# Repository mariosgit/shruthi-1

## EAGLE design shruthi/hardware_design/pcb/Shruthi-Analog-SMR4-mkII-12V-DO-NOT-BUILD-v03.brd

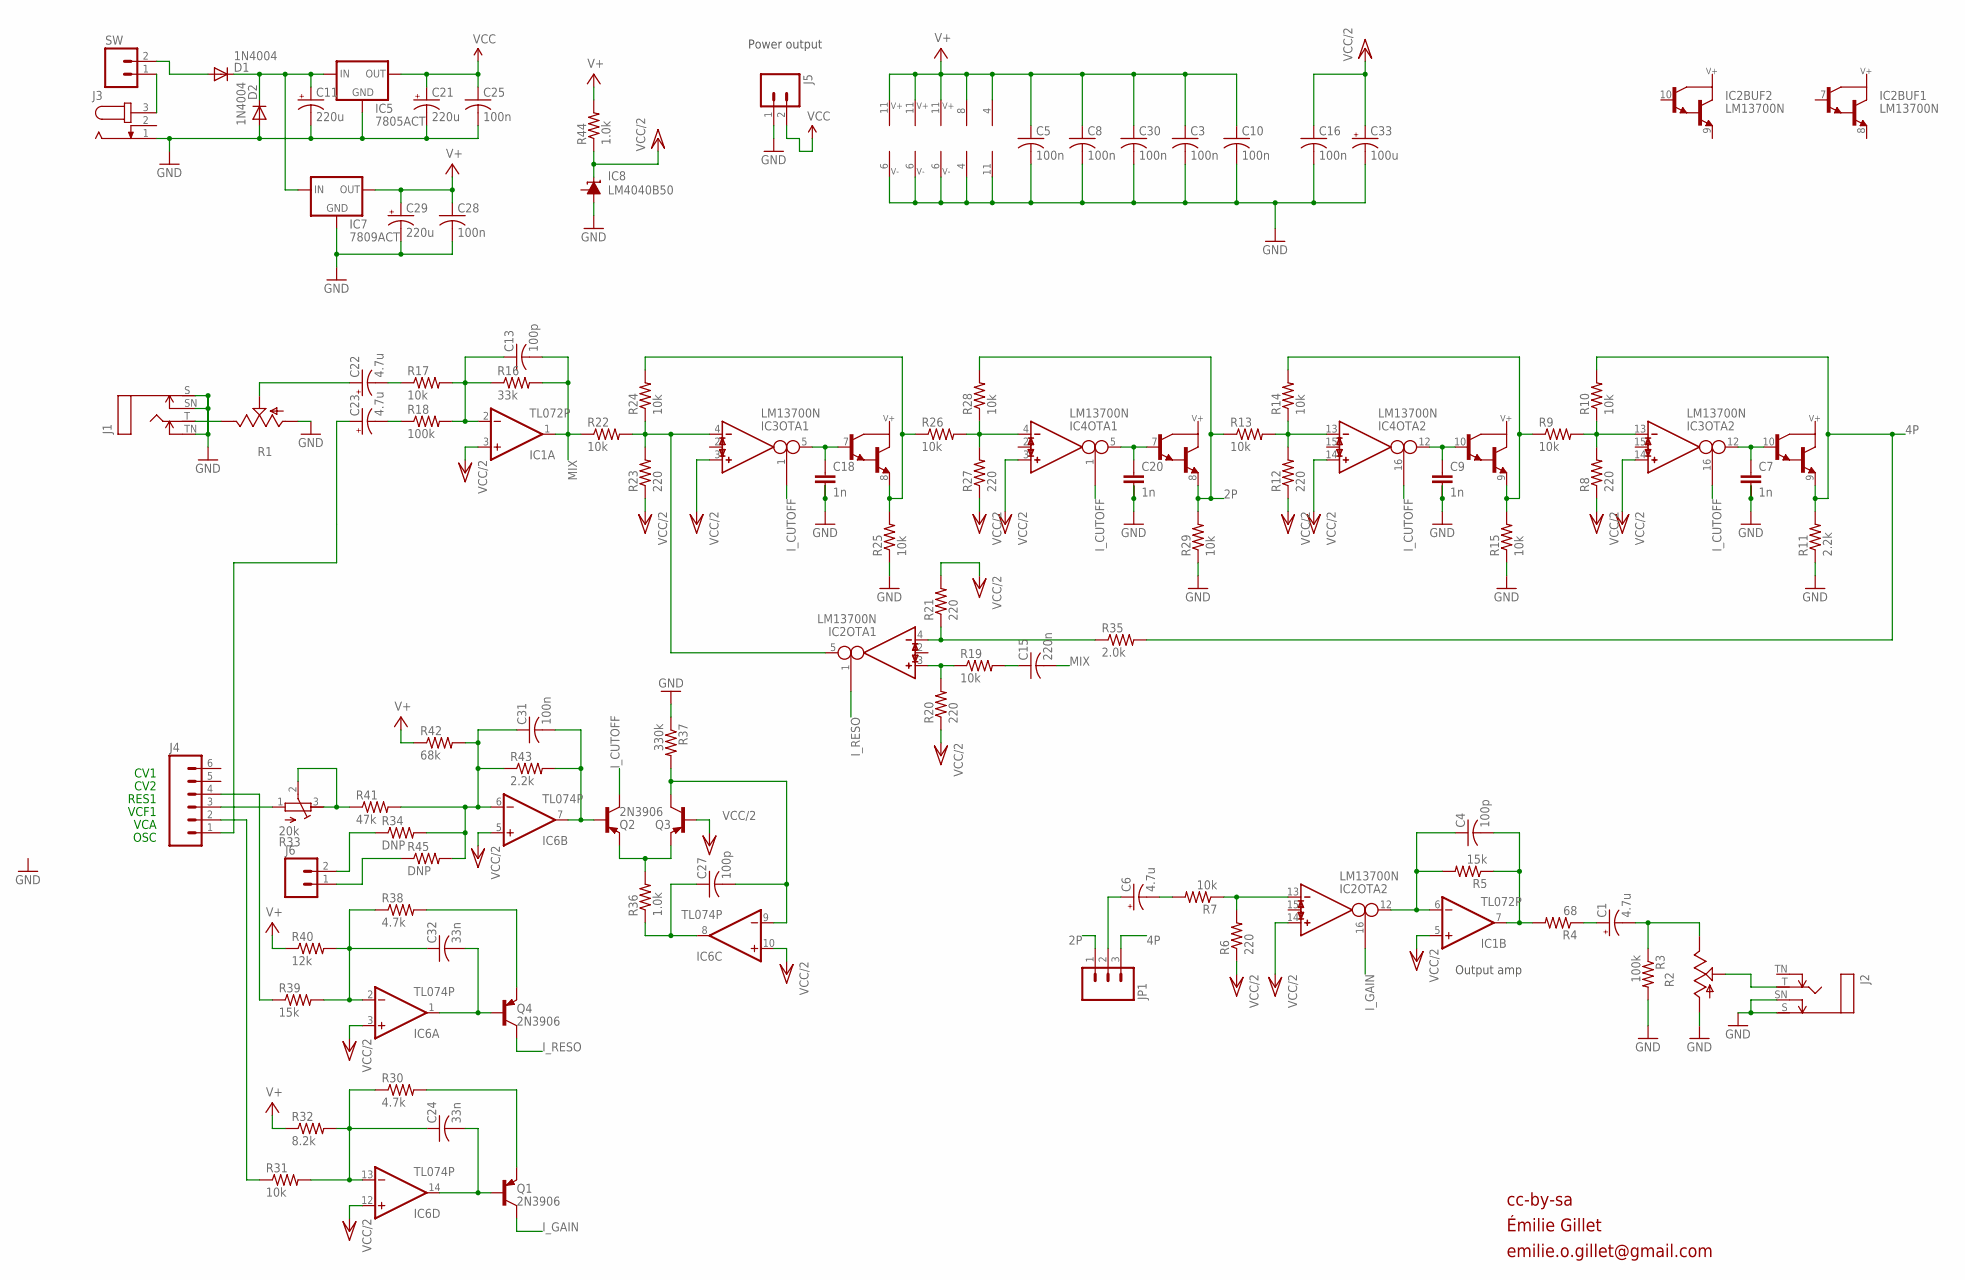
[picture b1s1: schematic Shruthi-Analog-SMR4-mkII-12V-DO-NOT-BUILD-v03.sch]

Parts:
C1, C6, C22, C23: 4.7u; E2,5-6
C3, C5, C8, C10, C16, C25, C28, C30, C31: 100n; C025-025X050
C4, C13, C27: 100p; C025-025X050
C7, C9, C18, C20: 1n; C2.5/5-2
C11, C21, C29: 220u; E5-10,5
C15: 220n; C025-025X050
C24, C32: 33n; C050-025X075
C33: 100u; E2,5-6
D1, D2: 1N4004; DO41-10
IC1: TL072P; DIL08
IC2, IC3, IC4: LM13700N; DIL16
IC5: 7805ACT; 78XXS
IC6: TL074P; DIL14
IC7: 7809ACT; 78XXS
IC8: LM4040B50; LP_O-PBCY-W3
J1, J2: MONOSWS; NMJ4HC-S
J3: JACK-PLUG2; SPC4078_BIG_HOLES
J4: M06SIP; 1X06
J5, J6: M02PTH; 1X02
JP1: M03PTH; 1X03
Q1, Q2, Q3, Q4: 2N3906; TO92-
R1, R2: POT_USCABLED; CABLE_POT_6MM
R3, R18: 100k; 0204/7
R4: 68; 0204/7
R5, R39: 15k; 0204/7
R6, R8, R12, R20, R21, R23, R27: 220; 0204/7
R7, R9, R10, R13, R14, R15, R17, R19, R22, R24, R25, R26, R28, R29, R31: 10k; 0204/7
R11, R43: 2.2k; 0204/7
R16: 33k; 0204/7
R30, R38: 4.7k; 0204/7
R32: 8.2k; 0204/7
R33: 20k; RTRIM3296W
R34, R45: DNP; 0204V
R35: 2.0k; 0204/7
R36, R44: 1.0k; 0204/7
R37: 330k; 0204/7
R40: 12k; 0204/7
R41: 47k; 0204/7
R42: 68k; 0204/7
SW: M02PTH; 1X02

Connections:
2P: IC4.8 (E), JP1.1, R13.1, R28.2, R29.2
4P: IC3.9 (E), JP1.3, R10.2, R11.2, R35.2
GND: C3.2, C5.2, C7.2, C7.3, C8.2, C9.2, C9.3, C10.2, C11.-, C16.2, C18.2, C18.3, C20.2, C20.3, C21.-, C25.2, C28.2, C29.-, C30.2, C33.-, D2.A, IC1.4 (V-), IC2.6 (V-), IC3.6 (V-), IC4.6 (V-), IC5.GND, IC6.11 (V-), IC7.GND, IC8.3 (A), J1.S, J1.SN, J1.TN, J2.S, J2.SN, J3.1, J5.1, R1.A, R2.A, R3.2, R11.1, R15.1, R25.1, R29.1, R37.1
I_CUTOFF: IC3.1 (I_BIAS), IC3.16 (I_BIAS), IC4.1 (I_BIAS), IC4.16 (I_BIAS), Q2.1 (C)
I_GAIN: IC2.16 (I_BIAS), Q1.1 (C)
I_RESO: IC2.1 (I_BIAS), Q4.1 (C)
MIX: C13.2, C15.2, IC1.1 (OUT), R16.2, R22.1
unnamed: D1.A, SW.2
unnamed: C31.2, IC6.7 (OUT), Q2.2 (B), R43.2
unnamed: J3.3, SW.1
unnamed: C11.+, D1.C, D2.C, IC5.IN, IC7.IN
unnamed: J4.3, R33.1 (E)
unnamed: C13.1, IC1.2 (-IN), R16.1, R17.2, R18.2
unnamed: Q2.3 (E), Q3.3 (E), R36.2
unnamed: C6.+, JP1.2
unnamed: C27.1, IC6.8 (OUT), R36.1
unnamed: C27.2, IC6.9 (-IN), Q3.1 (C), R37.2
unnamed: J4.4, R39.1
unnamed: IC2.5 (OUT), IC3.4 (IN_N), R22.2, R23.2, R24.1
unnamed: J2.T, R2.S
unnamed: IC3.8 (E), R24.2, R25.2, R26.1
unnamed: IC4.4 (IN_N), R26.2, R27.2, R28.1
unnamed: C6.-, R7.2
unnamed: J6.2, R34.1
unnamed: C20.1, IC4.5 (OUT), IC4.7 (B)
unnamed: IC4.13 (IN_N), R12.2, R13.2, R14.1
unnamed: C15.1, R19.2
unnamed: J6.1, R45.1
unnamed: C9.1, IC4.10 (B), IC4.12 (OUT)
unnamed: IC3.13 (IN_N), R8.2, R9.2, R10.1
unnamed: C1.+, R4.1
unnamed: IC4.9 (E), R9.1, R14.2, R15.2
unnamed: C7.1, IC3.10 (B), IC3.12 (OUT)
unnamed: IC2.4 (IN_N), R21.1, R35.1
unnamed: C32.2, IC6.1 (OUT), Q4.2 (B)
unnamed: C24.2, IC6.14 (OUT), Q1.2 (B)
unnamed: C1.-, R2.E, R3.1
unnamed: IC2.3 (IN_P), R19.1, R20.2
unnamed: IC2.13 (IN_N), R6.2, R7.1
unnamed: C23.+, J4.1
unnamed: J1.T, R1.E
unnamed: C23.-, R18.1
unnamed: C31.1, IC6.6 (-IN), R34.2, R41.2, R42.2, R43.1, R45.2
unnamed: R33.2 (S), R33.3 (A), R41.1
unnamed: J4.2, R31.1
unnamed: C24.1, IC6.13 (-IN), R30.1, R31.2, R32.2
unnamed: C32.1, IC6.2 (-IN), R38.1, R39.2, R40.2
unnamed: Q4.3 (E), R38.2
unnamed: C4.2, IC1.7 (OUT), R4.2, R5.1
unnamed: C18.1, IC3.5 (OUT), IC3.7 (B)
unnamed: C22.+, R1.S
unnamed: Q1.3 (E), R30.2
unnamed: C4.1, IC1.6 (-IN), IC2.12 (OUT), R5.2
unnamed: C22.-, R17.1
V+: C3.1, C5.1, C8.1, C10.1, C28.1, C29.+, C30.1, IC1.8 (V+), IC2.11 (V+), IC3.11 (V+), IC4.11 (V+), IC6.4 (V+), IC7.OUT, R32.1, R40.1, R42.1, R44.2
VCC: C21.+, C25.1, IC5.OUT, J5.2
VCC/2: C16.1, C33.+, IC1.3 (+IN), IC1.5 (+IN), IC2.14 (IN_P), IC3.3 (IN_P), IC3.14 (IN_P), IC4.3 (IN_P), IC4.14 (IN_P), IC6.3 (+IN), IC6.5 (+IN), IC6.10 (+IN), IC6.12 (+IN), IC8.2 (C), Q3.2 (B), R6.1, R8.1, R12.1, R20.1, R21.2, R23.1, R27.1, R44.1

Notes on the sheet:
Power output
OSC
VCA
VCF1
RES1
cc-by-sa
Output amp
CV1
CV2
Émilie Gillet
emilie.o.gillet@gmail.com

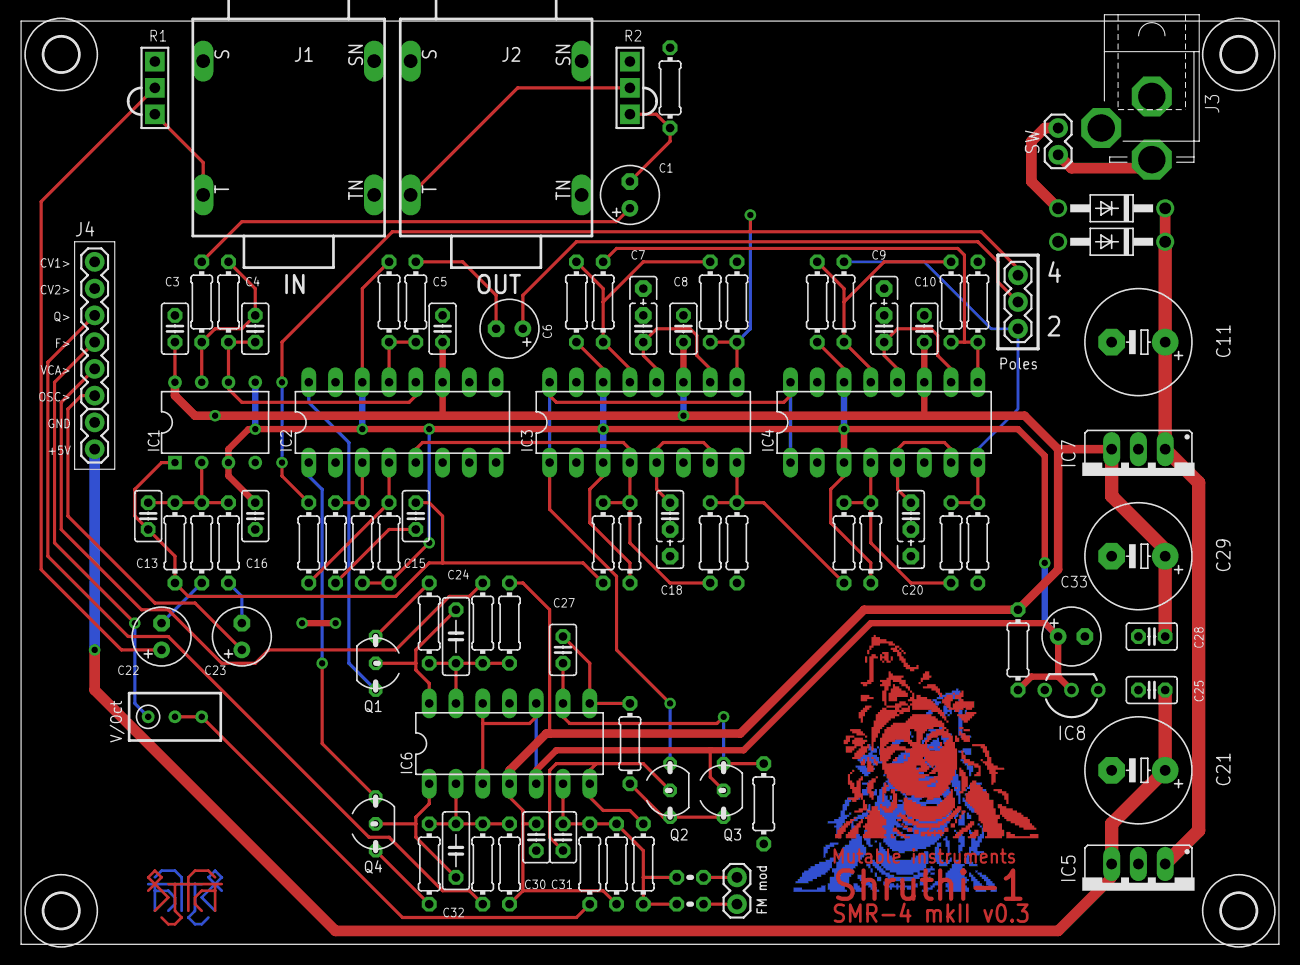
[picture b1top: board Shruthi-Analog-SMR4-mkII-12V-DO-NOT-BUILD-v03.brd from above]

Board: 2 copper layers, 119.4 x 87.6 mm, 100 parts (1 on the bottom side), 57 nets.

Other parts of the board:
U$1, U$2, U$4, U$5: 3,3
U$3, U$100: SARASWATI_COPPER

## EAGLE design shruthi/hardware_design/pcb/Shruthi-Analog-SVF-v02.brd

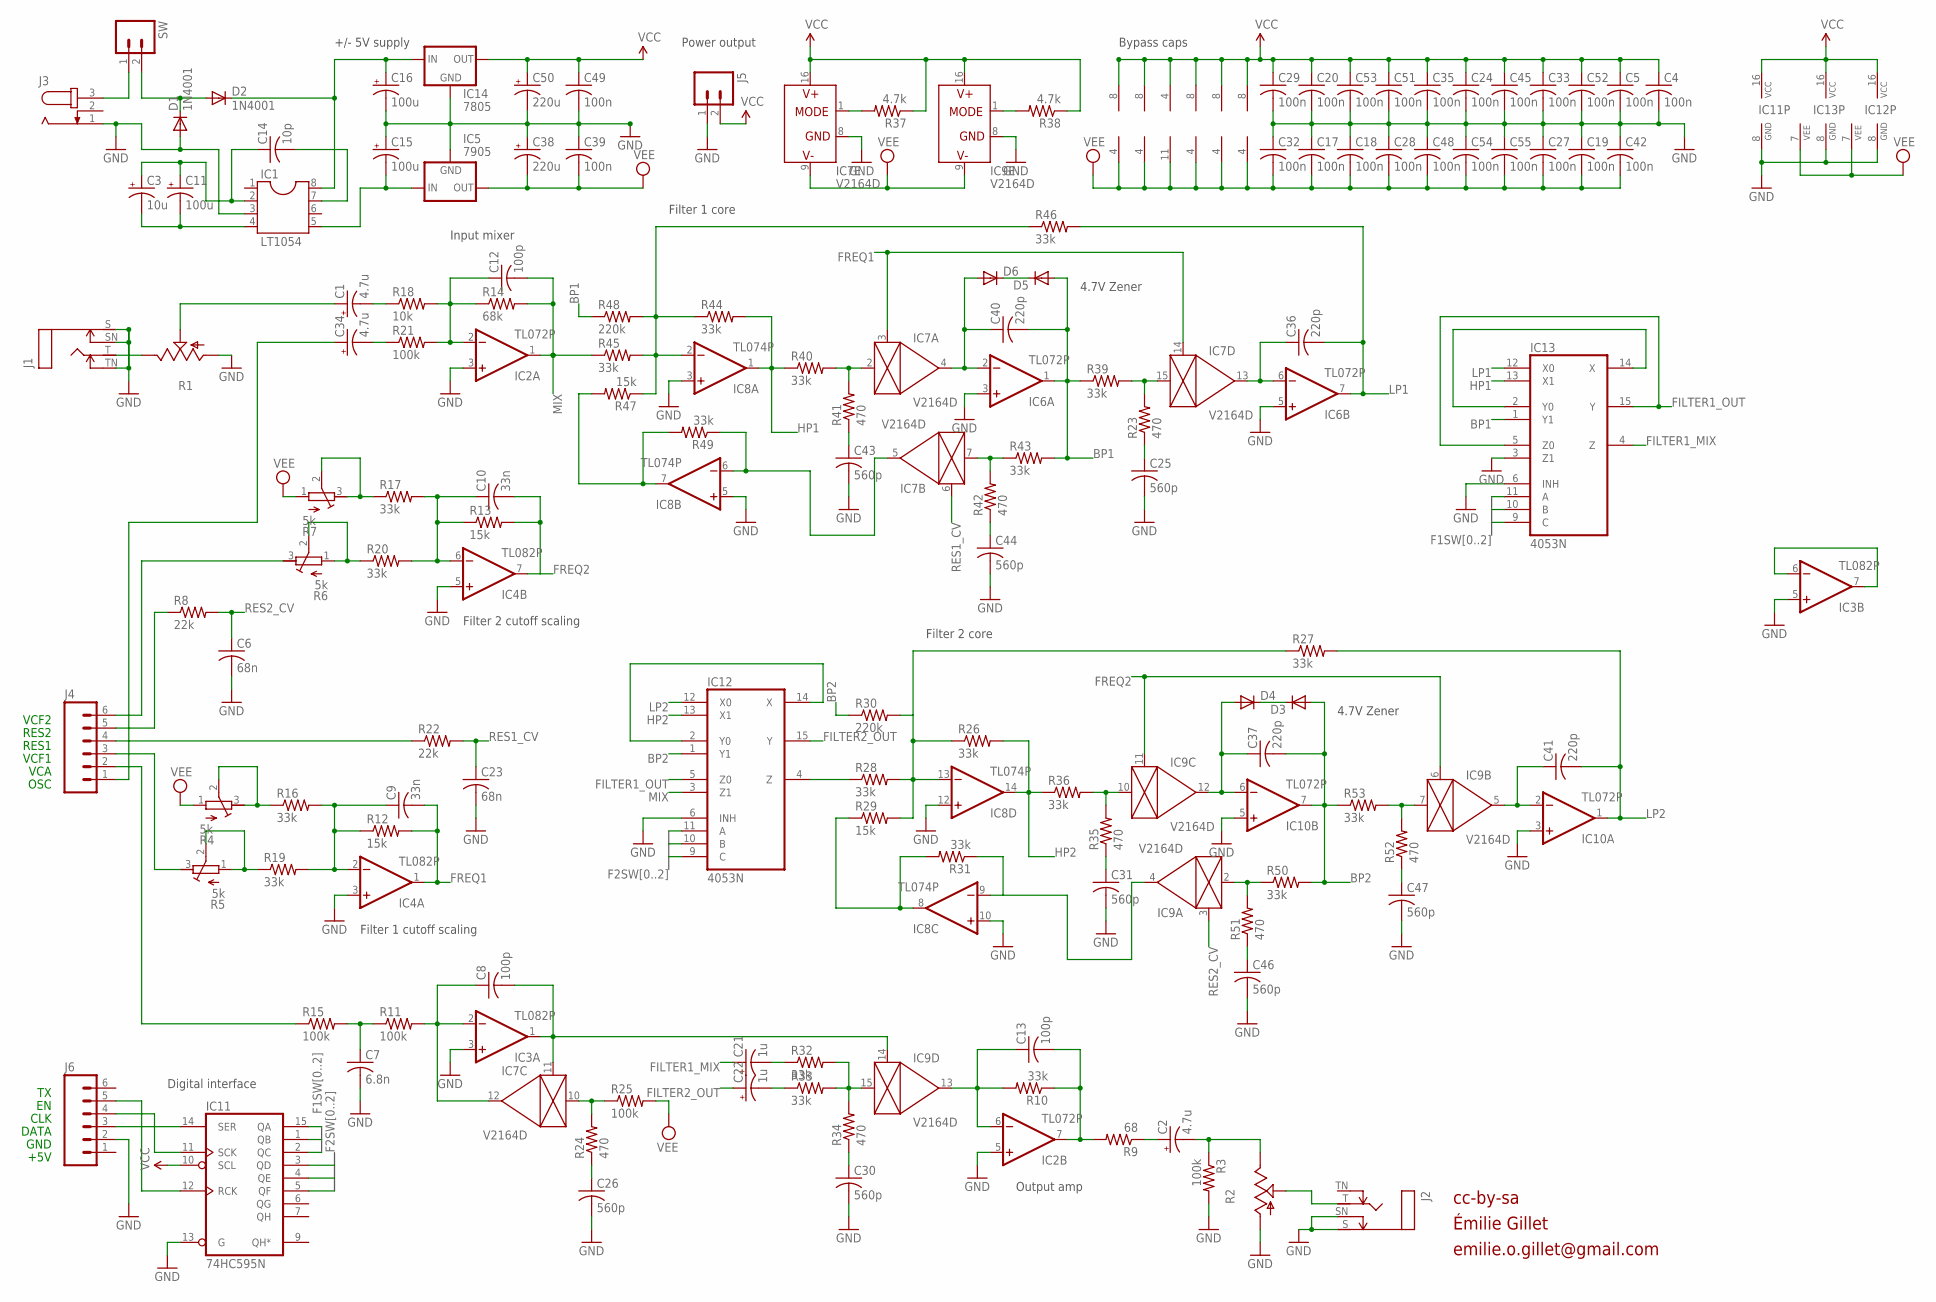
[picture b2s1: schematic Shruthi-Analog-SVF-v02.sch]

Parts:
C1, C2, C34: 4.7u; E2,5-6
C3: 10u; E2,5-5
C4, C5, C17, C18, C19, C20, C24, C27, C28, C29, C32, C33, C35, C39, C42, C45, C48, C49, C51, C52, C53, C54, C55: 100n; C025-025X050
C6, C23: 68n; C050-025X075
C7: 6.8n; C025-025X050
C8, C12, C13: 100p; C025-025X050
C9, C10: 33n; C050-025X075
C11: 100u; E2,5-6
C14: 10p; C025-025X050
C15, C16: 100u; E2,5-7
C21, C22: 1u; E2,5-5
C25, C26, C30, C31, C43, C44, C46, C47: 560p; C025-025X050
C36, C37, C40, C41: 220p; C025-025X050
C38, C50: 220u; E5-10,5
D1, D2: 1N4001; DO41-10
D3, D4, D5, D6: DIODE-D-5; D-5
IC1: LT1054; DIL08
IC2, IC6, IC10: TL072P; DIL08
IC3, IC4: TL082P; DIL08
IC5: 7905; 79XXS
IC7, IC9: V2164D; DIL16
IC8: TL074P; DIL14
IC11: 74HC595N; DIL16
IC12, IC13: 4053N; DIL16
IC14: 7805; 78XXS
J1, J2: MONOSWS; NMJ4HC-S
J3: JACK-PLUG1; SPC4078
J4, J6: M06SIP; 1X06
J5: M02PTH; 1X02
R1, R2: POT_USCABLED; CABLE_POT_6MM
R3, R11, R15, R21, R25: 100k; 0204/7
R4, R5, R6, R7: 5k; RTRIM3296W
R8, R22: 22k; 0204/7
R9: 68; 0204/7
R10, R16, R17, R19, R20, R26, R27, R28, R31, R32, R33, R36, R39, R40, R43, R44, R45, R46, R49, R50, R53: 33k; 0204/7
R12, R13, R29, R47: 15k; 0204/7
R14: 68k; 0204/7
R18: 10k; 0204/7
R23, R24, R34, R35, R41, R42, R51, R52: 470; 0204/7
R30, R48: 220k; 0204/7
R37, R38: 4.7k; 0204/7
SW: M02PTH; 1X02

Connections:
BP1: C40.2, D5.A, IC6.1 (OUT), IC13.1 (Y1), R39.1, R43.2, R48.1
BP2: C37.2, D3.A, IC10.7 (OUT), IC12.1 (Y1), R30.1, R50.2, R53.1
F1SW0: IC11.15 (QA), IC13.9 (C)
F1SW1: IC11.1 (QB), IC13.10 (B)
F1SW2: IC11.2 (QC), IC13.11 (A)
F2SW0: IC11.3 (QD), IC12.9 (C)
F2SW1: IC11.4 (QE), IC12.10 (B)
F2SW2: IC11.5 (QF), IC12.11 (A)
FILTER1_MIX: C21.+, IC13.4 (Z)
FILTER1_OUT: IC12.5 (Z0), IC13.5 (Z0), IC13.15 (Y)
FILTER2_OUT: C22.+, IC12.15 (Y)
FREQ1: C9.2, IC4.1 (OUT), IC7.3 (CTRL), IC7.14 (CTRL), R12.2
FREQ2: C10.2, IC4.7 (OUT), IC9.6 (CTRL), IC9.11 (CTRL), R13.2
GND: C4.2, C5.2, C6.2, C7.2, C15.+, C16.-, C17.1, C18.1, C19.1, C20.2, C23.2, C24.2, C25.2, C26.2, C27.1, C28.1, C29.2, C30.2, C31.2, C32.1, C33.2, C35.2, C38.+, C39.1, C42.1, C43.2, C44.2, C45.2, C46.2, C47.2, C48.1, C49.2, C50.-, C51.2, C52.2, C53.2, C54.1, C55.1, D1.A, IC1.3, IC2.3 (+IN), IC2.5 (+IN), IC3.3 (+IN), IC3.5 (+IN), IC4.3 (+IN), IC4.5 (+IN), IC5.GND, IC6.3 (+IN), IC6.5 (+IN), IC7.8 (GND), IC8.3 (+IN), IC8.5 (+IN), IC8.10 (+IN), IC8.12 (+IN), IC9.8 (GND), IC10.3 (+IN), IC10.5 (+IN), IC11.8 (GND), IC11.13 (G), IC12.6 (INH), IC12.8 (GND), IC13.3 (Z1), IC13.6 (INH), IC13.8 (GND), IC14.GND, J1.S, J1.SN, J1.TN, J2.S, J2.SN, J3.1, J5.1, J6.2, R1.A, R2.A, R3.2
HP1: IC8.1 (OUT), IC13.13 (X1), R40.1, R44.2
HP2: IC8.14 (OUT), IC12.13 (X1), R26.2, R36.1
LP1: C36.2, IC6.7 (OUT), IC13.12 (X0), R46.2
LP2: C41.2, IC10.1 (OUT), IC12.12 (X0), R27.2
MIX: C12.2, IC2.1 (OUT), IC12.3 (Z1), R14.2, R45.1
unnamed: C3.+, C11.+, C14.1, IC1.2
unnamed: C10.1, IC4.6 (-IN), R13.1, R17.2, R20.2
unnamed: J3.3, SW.1
unnamed: C16.+, D2.C, IC1.8, IC14.IN
unnamed: C3.-, C11.-, IC1.4
unnamed: C12.1, IC2.2 (-IN), R14.1, R18.2, R21.2
unnamed: R6.1 (E), R6.2 (S), R20.1
unnamed: J4.6, R6.3 (A)
unnamed: R7.2 (S), R7.3 (A), R17.1
unnamed: IC7.10 (IN), R24.2, R25.1
unnamed: C8.1, IC3.2 (-IN), IC7.12 (OUT), R11.2
unnamed: IC8.2 (-IN), R44.1, R45.2, R46.1, R47.1, R48.2
unnamed: IC11.12 (RCK), J6.5
unnamed: IC11.14 (SER), J6.3
unnamed: IC11.11 (SCK), J6.4
unnamed: C25.1, R23.1
unnamed: IC8.13 (-IN), R26.1, R27.1, R28.2, R29.2, R30.2
unnamed: C40.1, D6.A, IC6.2 (-IN), IC7.4 (OUT)
unnamed: C37.1, D4.A, IC9.12 (OUT), IC10.6 (-IN)
unnamed: IC7.7 (IN), R42.2, R43.1
unnamed: C7.1, R11.1, R15.2
unnamed: IC8.8 (OUT), R29.1, R31.2
unnamed: IC9.2 (IN), R50.1, R51.2
unnamed: C2.+, R9.1
unnamed: IC7.15 (IN), R23.2, R39.2
unnamed: C44.1, R42.1
unnamed: C36.1, IC6.6 (-IN), IC7.13 (OUT)
unnamed: IC7.2 (IN), R40.2, R41.2
unnamed: C43.1, R41.1
unnamed: IC7.5 (OUT), IC8.6 (-IN), R49.1
unnamed: C2.-, R2.E, R3.1
unnamed: D3.C, D4.C
unnamed: IC9.7 (IN), R52.2, R53.2
unnamed: C34.+, J4.1
unnamed: C14.2, IC1.7
unnamed: IC8.9 (-IN), IC9.4 (OUT), R31.1
unnamed: J1.T, R1.E
unnamed: C34.-, R21.1
unnamed: C9.1, IC4.2 (-IN), R12.1, R16.2, R19.2
unnamed: R5.1 (E), R5.2 (S), R19.1
unnamed: J4.3, R5.3 (A)
unnamed: R4.2 (S), R4.3 (A), R16.1
unnamed: C41.1, IC9.5 (OUT), IC10.2 (-IN)
unnamed: J4.2, R15.1
unnamed: C47.1, R52.1
unnamed: J2.T, R2.S
unnamed: IC8.7 (OUT), R47.2, R49.2
unnamed: C46.1, R51.1
unnamed: IC9.10 (IN), R35.2, R36.2
unnamed: C31.1, R35.1
unnamed: D5.C, D6.C
unnamed: C8.2, IC3.1 (OUT), IC7.11 (CTRL), IC9.14 (CTRL)
unnamed: C21.-, R32.1
unnamed: C15.-, IC1.5, IC5.IN
unnamed: D1.C, D2.A, SW.2
unnamed: C22.-, R33.1
unnamed: IC3.6 (-IN), IC3.7 (OUT)
unnamed: IC13.2 (Y0), IC13.14 (X)
unnamed: C13.2, IC2.7 (OUT), R9.2, R10.1
unnamed: C26.1, R24.1
unnamed: C30.1, R34.1
unnamed: C1.+, R1.S
unnamed: IC9.15 (IN), R32.2, R33.2, R34.2
unnamed: IC7.1 (MODE), R37.2
unnamed: J4.4, R22.1
unnamed: C13.1, IC2.6 (-IN), IC9.13 (OUT), R10.2
unnamed: IC9.1 (MODE), R38.2
unnamed: C1.-, R18.1
unnamed: J4.5, R8.1
unnamed: IC12.2 (Y0), IC12.14 (X)
unnamed: IC12.4 (Z), R28.1
RES1_CV: C23.1, IC7.6 (CTRL), R22.2
RES2_CV: C6.1, IC9.3 (CTRL), R8.2
VCC: C4.1, C5.1, C20.1, C24.1, C29.1, C33.1, C35.1, C45.1, C49.1, C50.+, C51.1, C52.1, C53.1, IC2.8 (V+), IC3.8 (V+), IC4.8 (V+), IC6.8 (V+), IC7.16 (V+), IC8.4 (V+), IC9.16 (V+), IC10.8 (V+), IC11.10 (SCL), IC11.16 (VCC), IC12.16 (VCC), IC13.16 (VCC), IC14.OUT, J5.2, R37.1, R38.1
VEE: C17.2, C18.2, C19.2, C27.2, C28.2, C32.2, C38.-, C39.2, C42.2, C48.2, C54.2, C55.2, IC2.4 (V-), IC3.4 (V-), IC4.4 (V-), IC5.OUT, IC6.4 (V-), IC7.9 (V-), IC8.11 (V-), IC9.9 (V-), IC10.4 (V-), IC12.7 (VEE), IC13.7 (VEE), R4.1 (E), R7.1 (E), R25.2

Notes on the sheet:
Power output
OSC
VCA
VCF1
RES1
Input mixer
Filter 1 cutoff scaling
cc-by-sa
+/- 5V supply
Bypass caps
Output amp
VCF2
RES2
+5V
GND
DATA
CLK
Digital interface
Filter 2 cutoff scaling
Filter 1 core
Filter 2 core
4.7V Zener
Émilie Gillet
emilie.o.gillet@gmail.com

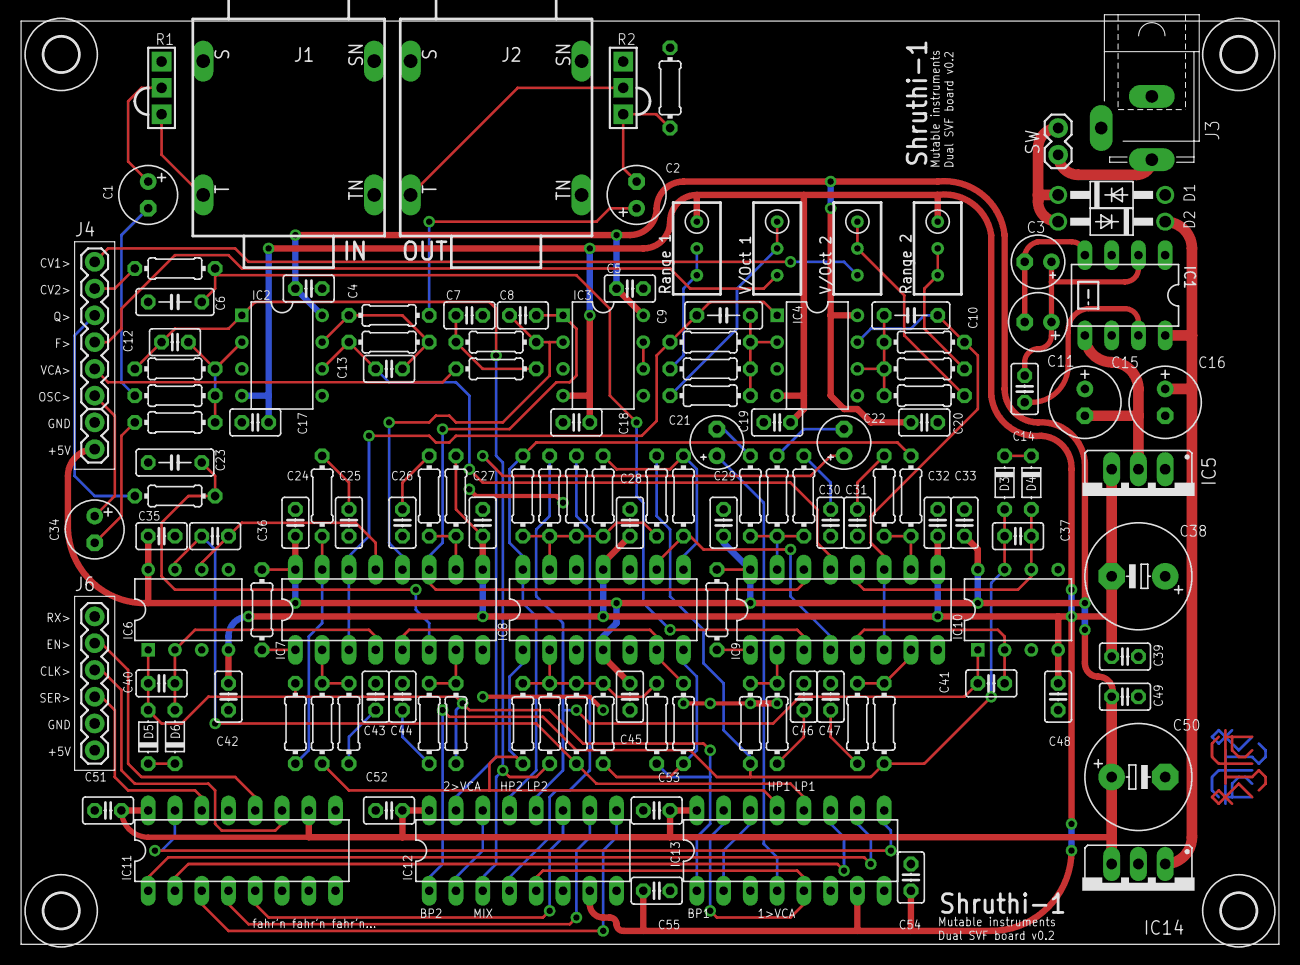
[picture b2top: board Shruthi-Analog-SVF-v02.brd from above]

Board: 2 copper layers, 119.4 x 87.6 mm, 141 parts (0 on the bottom side), 94 nets.

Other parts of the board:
U$1, U$2, U$5, U$6: 3,3
U$3, U$4: DURGA

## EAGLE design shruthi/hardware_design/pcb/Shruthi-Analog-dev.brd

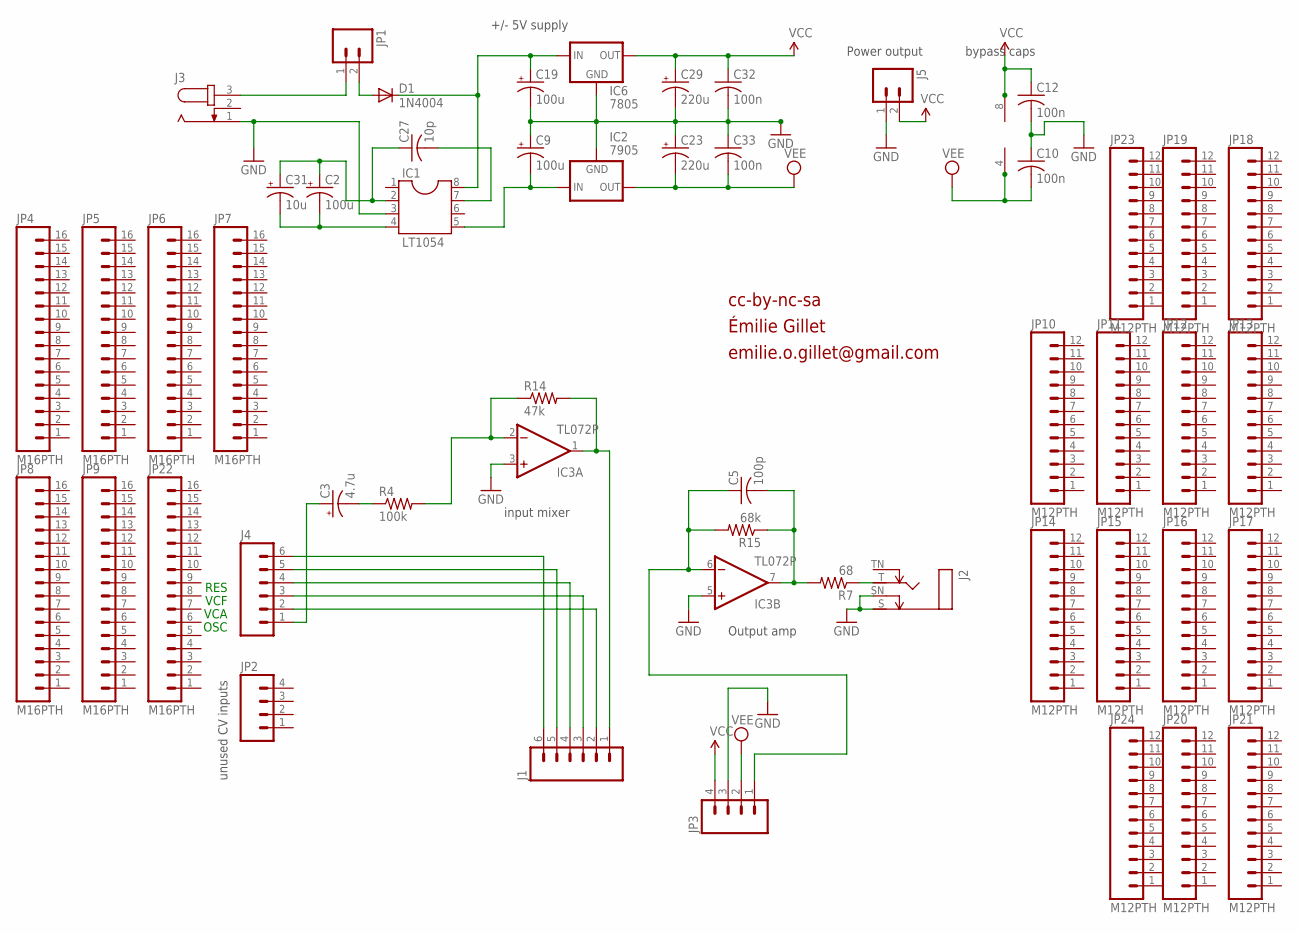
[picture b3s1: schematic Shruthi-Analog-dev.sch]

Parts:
C2: 100u; E2,5-6
C3: 4.7u; E2,5-6
C5: 100p; C025-025X050
C9, C19: 100u; E2,5-7
C10, C12, C32, C33: 100n; C025-025X050
C23, C29: 220u; E5-10,5
C27: 10p; C025-025X050
C31: 10u; E2,5-5
D1: 1N4004; DO41-10
IC1: LT1054; DIL08
IC2: 7905; 79XXS
IC3: TL072P; DIL08
IC6: 7805; 78XXS
J1, J4: M06SIP; 1X06
J2: MONOSWS; NMJ4HC-S
J3: JACK-PLUG; SPC4078_LARGER_HOLES
J5: M02PTH; 1X02
JP1: M02; 1X02_LONGPADS
JP2, JP3: M04PTH; 1X04
JP4, JP5, JP6, JP7, JP8, JP9, JP22: M16PTH; 1X16
JP10, JP11, JP12, JP13, JP14, JP15, JP16, JP17, JP18, JP19, JP20, JP21, JP23, JP24: M12PTH; 1X12
R4: 100k; 0204/7
R7: 68; 0204/7
R14: 47k; 0204/7
R15: 68k; 0204/7

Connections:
GND: C9.+, C10.1, C12.2, C19.-, C23.+, C29.-, C32.2, C33.1, IC1.3, IC2.GND, IC3.3 (+IN), IC3.5 (+IN), IC6.GND, J2.S, J2.SN, J3.1, J5.1, JP3.3
unnamed: C2.+, C27.1, C31.+, IC1.2
unnamed: J1.5, J4.5
unnamed: J3.3, JP1.1
unnamed: C19.+, D1.C, IC1.8, IC6.IN
unnamed: C2.-, C31.-, IC1.4
unnamed: J1.6, J4.6
unnamed: J1.3, J4.3
unnamed: IC3.1 (OUT), J1.1, R14.2
unnamed: C3.+, J4.1
unnamed: C27.2, IC1.7
unnamed: IC3.2 (-IN), R4.2, R14.1
unnamed: C3.-, R4.1
unnamed: J1.2, J4.2
unnamed: J2.T, R7.1
unnamed: J1.4, J4.4
unnamed: C9.-, IC1.5, IC2.IN
unnamed: D1.A, JP1.2
unnamed: C5.2, IC3.7 (OUT), R7.2, R15.1
unnamed: C5.1, IC3.6 (-IN), JP3.1, R15.2
VCC: C12.1, C29.+, C32.1, IC3.8 (V+), IC6.OUT, J5.2, JP3.4
VEE: C10.2, C23.-, C33.2, IC2.OUT, IC3.4 (V-), JP3.2

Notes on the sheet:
Power output
OSC
VCA
VCF
RES
unused CV inputs
input mixer
cc-by-nc-sa
+/- 5V supply
bypass caps
Output amp
Émilie Gillet
emilie.o.gillet@gmail.com

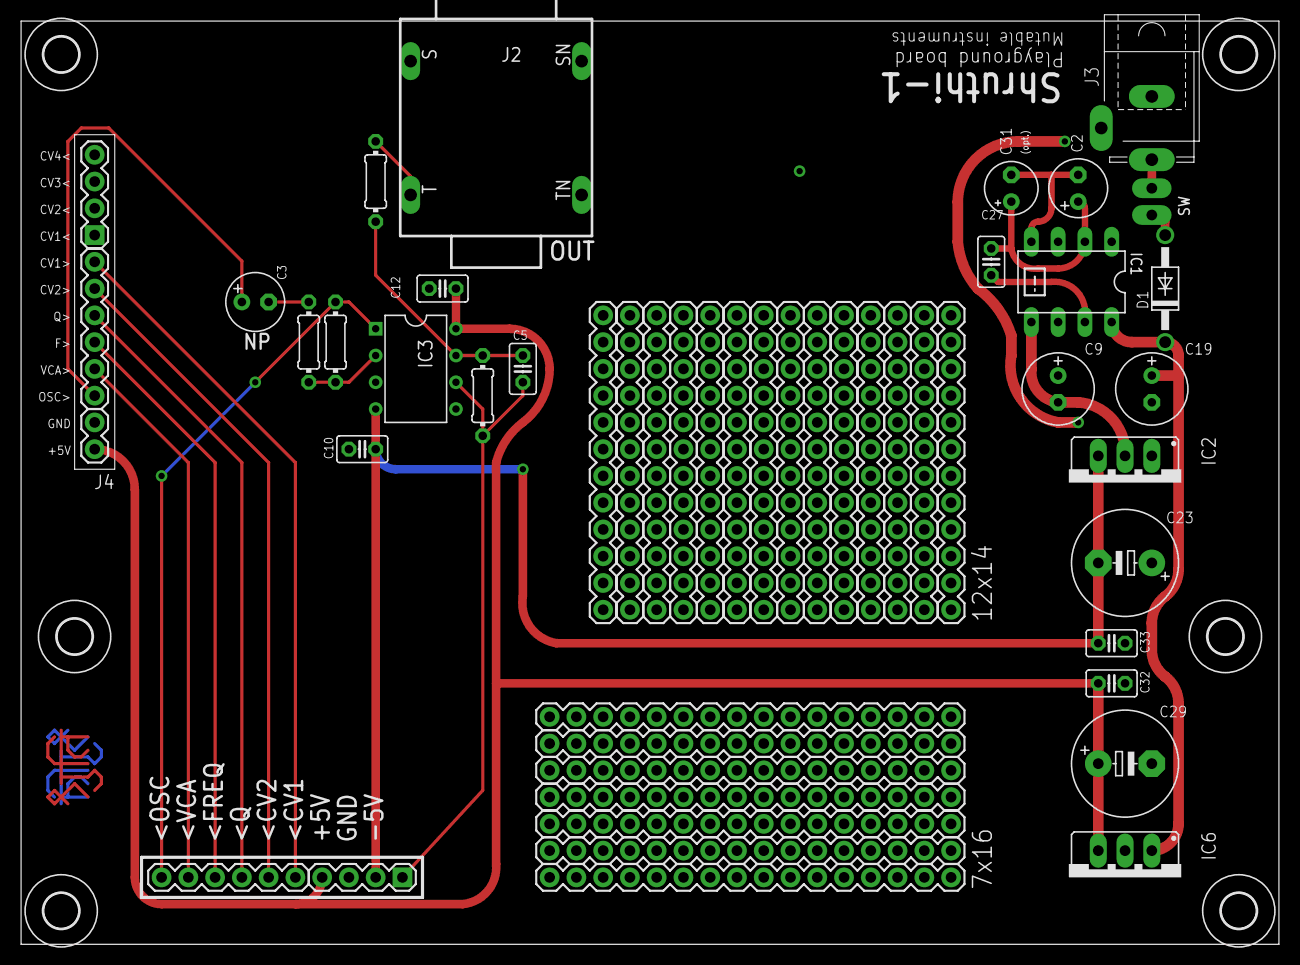
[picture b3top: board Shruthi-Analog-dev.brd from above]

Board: 2 copper layers, 119.4 x 87.6 mm, 57 parts (0 on the bottom side), 22 nets.

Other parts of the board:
U$1, U$2, U$3, U$4, U$5, U$6: 3,3

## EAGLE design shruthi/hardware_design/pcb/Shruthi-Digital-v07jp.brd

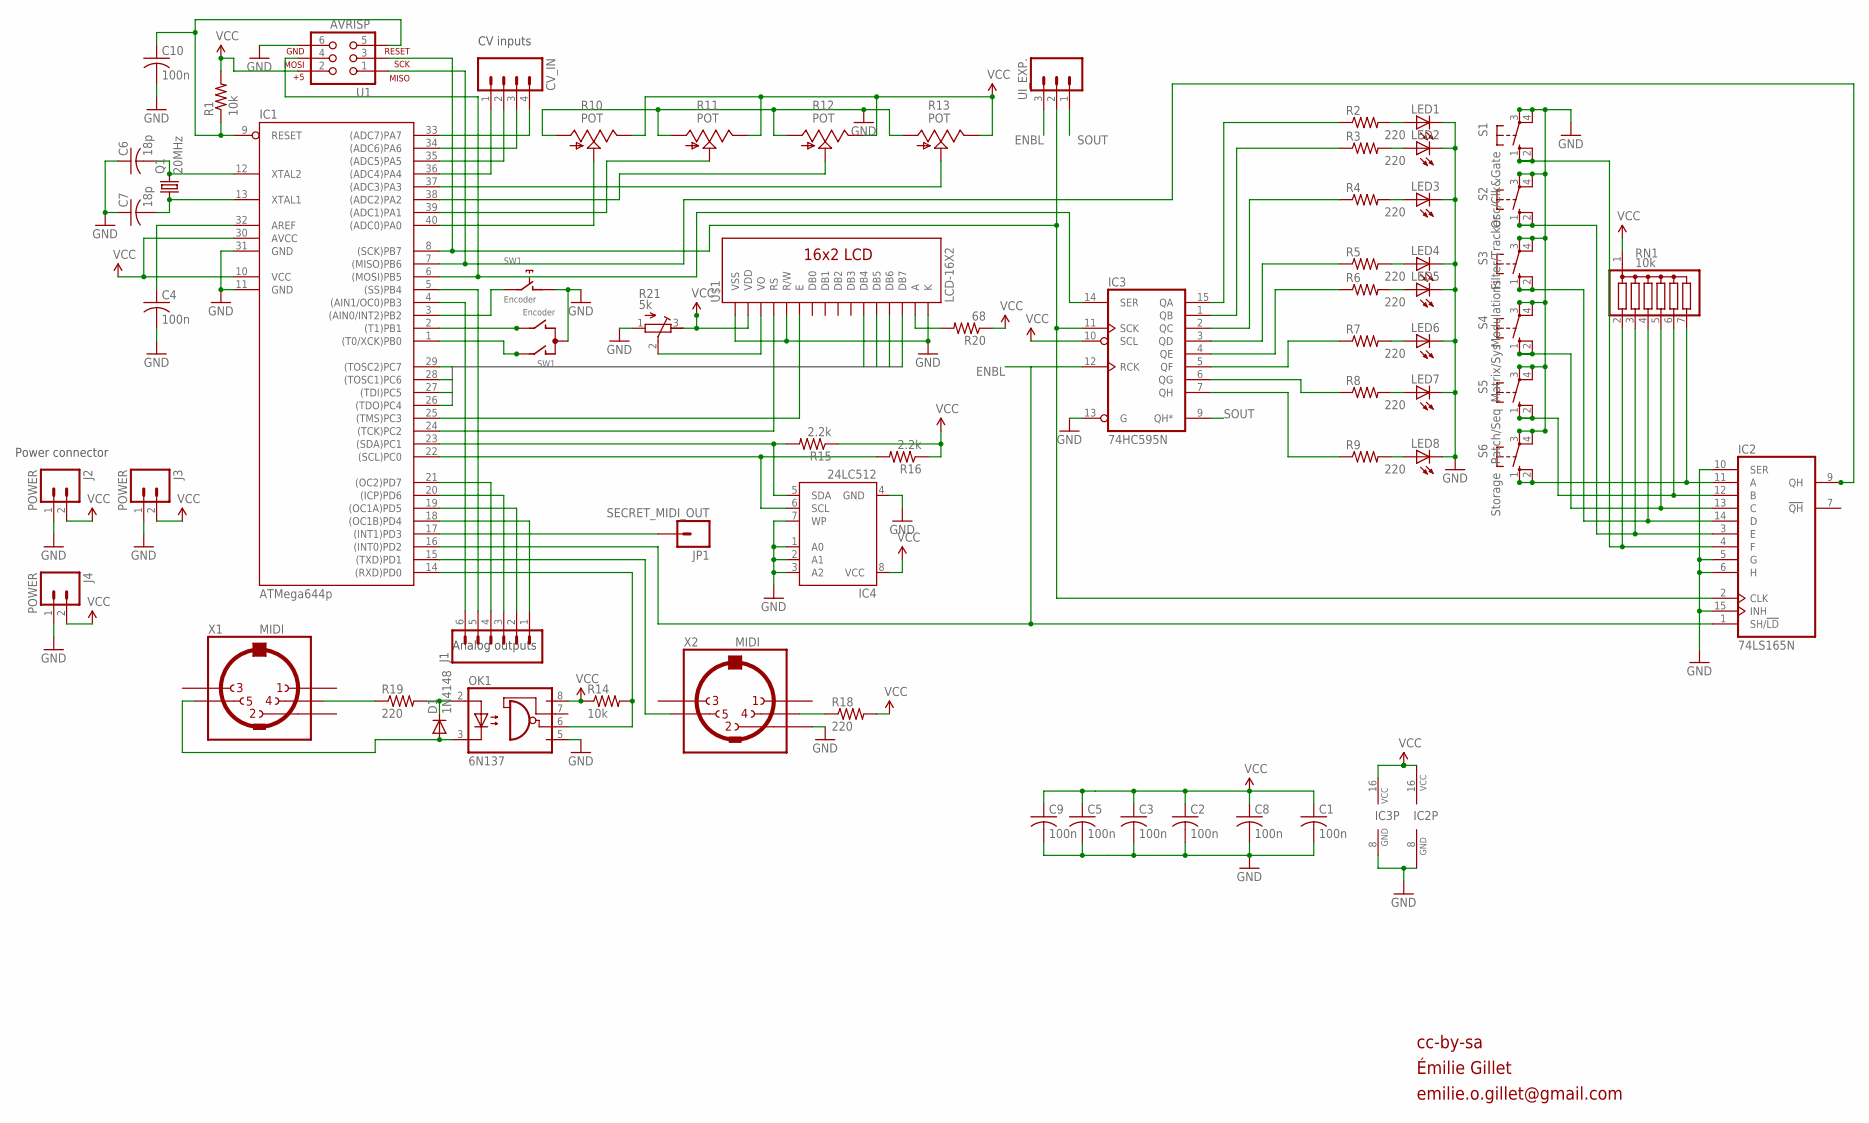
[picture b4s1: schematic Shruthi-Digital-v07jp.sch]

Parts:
C1, C2, C3, C4, C5, C8, C9, C10: 100n; C025-024X044
C6, C7: 18p; C025-024X044
CV_IN: M04PTH; 1X04
D1: 1N4148; D-5
IC1: ATMega644p; DIL40
IC2: 74LS165N; DIL16
IC3: 74HC595N; DIL16
IC4: 24LC512; DIL08
J1: M06SIP; 1X06
J2, J3, J4: POWER; 1X02
JP1: SECRET_MIDI_OUT; 1X01
LED1, LED2, LED3, LED4, LED5, LED6, LED7, LED8: LED3MM
OK1: 6N137; DIL08
Q1: 20MHz; HC49U-V
R1, R14: 10k; 0204/7
R2, R3, R4, R5, R6, R7, R8, R9, R18, R19: 220; 0204/7
R10, R11, R12, R13: POT; ALPS_POT_SFE
R15, R16: 2.2k; 0204/7
R20: 68; 0204/7
R21: 5k; RTRIM3296X
RN1: 10k; SIL7
S1: Osc/Clk&Gate; B3F-40XX
S2: Filter/Tracker; B3F-40XX
S3: Modulations; B3F-40XX
S4: Matrix/Sys; B3F-40XX
S5: Patch/Seq; B3F-40XX
S6: Storage; B3F-40XX
SW1: Encoder; ALPS_EC12E_SW
U1: AVRISP; 2X3
U$1: LCD-16X2
UI_EXP.: M03PTH; 1X03
X1, X2: MIDI; MAB5SH

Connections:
ENBL: IC1.16 ((INT0)PD2), IC2.1 (SH/!LD), IC3.12 (RCK), UI_EXP..3
GND: C1.2, C2.2, C3.2, C4.2, C5.2, C6.1, C7.1, C8.2, C9.2, C10.2, IC1.11 (GND), IC1.31 (GND), IC2.5 (G), IC2.6 (H), IC2.8 (GND), IC2.10 (SER), IC2.15 (INH), IC3.8 (GND), IC3.13 (G), IC4.1 (A0), IC4.2 (A1), IC4.3 (A2), IC4.4 (GND), IC4.7 (WP), J2.1, J3.1, J4.1, LED1.K (C), LED2.K (C), LED3.K (C), LED4.K (C), LED5.K (C), LED6.K (C), LED7.K (C), LED8.K (C), OK1.5 (GND), R10.P$3 (A), R11.P$3 (A), R12.P$3 (A), R13.P$3 (A), R21.1 (E), S1.3, S1.4 (P1), S2.3, S2.4 (P1), S3.3, S3.4 (P1), S4.3, S4.4 (P1), S5.3, S5.4 (P1), S6.3, S6.4 (P1), SW1.C, SW1.D (1), U1.6, U$1.1 (VSS), U$1.5 (R/W), U$1.16 (K), X2.2
LCD_DATA1: IC1.26 ((TDO)PC4), U$1.11 (DB4)
LCD_DATA2: IC1.27 ((TDI)PC5), U$1.12 (DB5)
LCD_DATA3: IC1.28 ((TOSC1)PC6), U$1.13 (DB6)
LCD_DATA4: IC1.29 ((TOSC2)PC7), U$1.14 (DB7)
unnamed: IC3.2 (QC), R4.1
unnamed: IC1.24 ((TCK)PC2), U$1.4 (RS)
unnamed: IC2.11 (A), RN1.7, S6.1 (S), S6.2 (S1)
unnamed: IC2.3 (E), RN1.3, S2.1 (S), S2.2 (S1)
unnamed: C10.1, IC1.9 (RESET), R1.1, U1.5
unnamed: C4.1, IC1.32 (AREF)
unnamed: IC1.8 ((SCK)PB7), IC2.2 (CLK), IC3.11 (SCK), U1.3, UI_EXP..2
unnamed: IC1.7 ((MISO)PB6), IC2.9 (QH), U1.1
unnamed: CV_IN.1, IC1.36 ((ADC4)PA4)
unnamed: CV_IN.2, IC1.35 ((ADC5)PA5)
unnamed: CV_IN.3, IC1.34 ((ADC6)PA6)
unnamed: CV_IN.4, IC1.33 ((ADC7)PA7)
unnamed: IC1.40 ((ADC0)PA0), R10.P$2 (S)
unnamed: IC1.39 ((ADC1)PA1), R11.P$2 (S)
unnamed: IC1.38 ((ADC2)PA2), R12.P$2 (S)
unnamed: IC1.37 ((ADC3)PA3), R13.P$2 (S)
unnamed: IC1.4 ((AIN1/OC0)PB3), J1.6
unnamed: IC1.5 ((SS)PB4), J1.5
unnamed: IC1.18 ((OC1B)PD4), J1.1
unnamed: IC1.19 ((OC1A)PD5), J1.2
unnamed: IC1.20 ((ICP)PD6), J1.3
unnamed: IC1.21 ((OC2)PD7), J1.4
unnamed: IC1.17 ((INT1)PD3), JP1.1
unnamed: IC1.23 ((SDA)PC1), IC4.5 (SDA), R15.2
unnamed: D1.C, OK1.2 (A), R19.2
unnamed: IC3.15 (QA), R2.1
unnamed: IC3.1 (QB), R3.1
unnamed: IC1.22 ((SCL)PC0), IC4.6 (SCL), R16.2
unnamed: IC3.3 (QD), R5.1
unnamed: IC3.4 (QE), R6.1
unnamed: IC3.5 (QF), R7.1
unnamed: IC3.7 (QH), R9.1
unnamed: IC3.6 (QG), R8.1
unnamed: LED1.A, R2.2
unnamed: LED2.A, R3.2
unnamed: LED3.A, R4.2
unnamed: LED4.A, R5.2
unnamed: LED5.A, R6.2
unnamed: LED6.A, R7.2
unnamed: LED7.A, R8.2
unnamed: LED8.A, R9.2
unnamed: IC1.6 ((MOSI)PB5), IC3.14 (SER), U1.4
unnamed: IC2.4 (F), RN1.2, S1.1 (S), S1.2 (S1)
unnamed: IC2.14 (D), RN1.4, S3.1 (S), S3.2 (S1)
unnamed: IC2.13 (C), RN1.5, S4.1 (S), S4.2 (S1)
unnamed: IC2.12 (B), RN1.6, S5.1 (S), S5.2 (S1)
unnamed: IC1.1 ((T0/XCK)PB0), SW1.A
unnamed: IC1.2 ((T1)PB1), SW1.B
unnamed: IC1.3 ((AIN0/INT2)PB2), SW1.E (2)
unnamed: R18.1, X2.4
unnamed: IC1.15 ((TXD)PD1), X2.5
unnamed: IC1.14 ((RXD)PD0), OK1.6 (VO), R14.2
unnamed: R19.1, X1.4
unnamed: D1.A, OK1.3 (C), X1.5
unnamed: IC1.25 ((TMS)PC3), U$1.6 (E)
unnamed: R21.2 (S), U$1.3 (VO)
unnamed: R20.2, U$1.15 (A)
unnamed: C7.2, IC1.13 (XTAL1), Q1.1
unnamed: C6.2, IC1.12 (XTAL2), Q1.2
SOUT: IC3.9 (QH*), UI_EXP..1
VCC: C1.1, C2.1, C3.1, C5.1, C8.1, C9.1, IC1.10 (VCC), IC1.30 (AVCC), IC2.16 (VCC), IC3.10 (SCL), IC3.16 (VCC), IC4.8 (VCC), J2.2, J3.2, J4.2, OK1.8 (VCC), R1.2, R10.P$1 (E), R11.P$1 (E), R12.P$1 (E), R13.P$1 (E), R14.1, R15.1, R16.1, R18.2, R20.1, R21.3 (A), RN1.1, U1.2, U$1.2 (VDD)

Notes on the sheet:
CV inputs
Power connector
Analog outputs
cc-by-sa
Émilie Gillet
emilie.o.gillet@gmail.com
